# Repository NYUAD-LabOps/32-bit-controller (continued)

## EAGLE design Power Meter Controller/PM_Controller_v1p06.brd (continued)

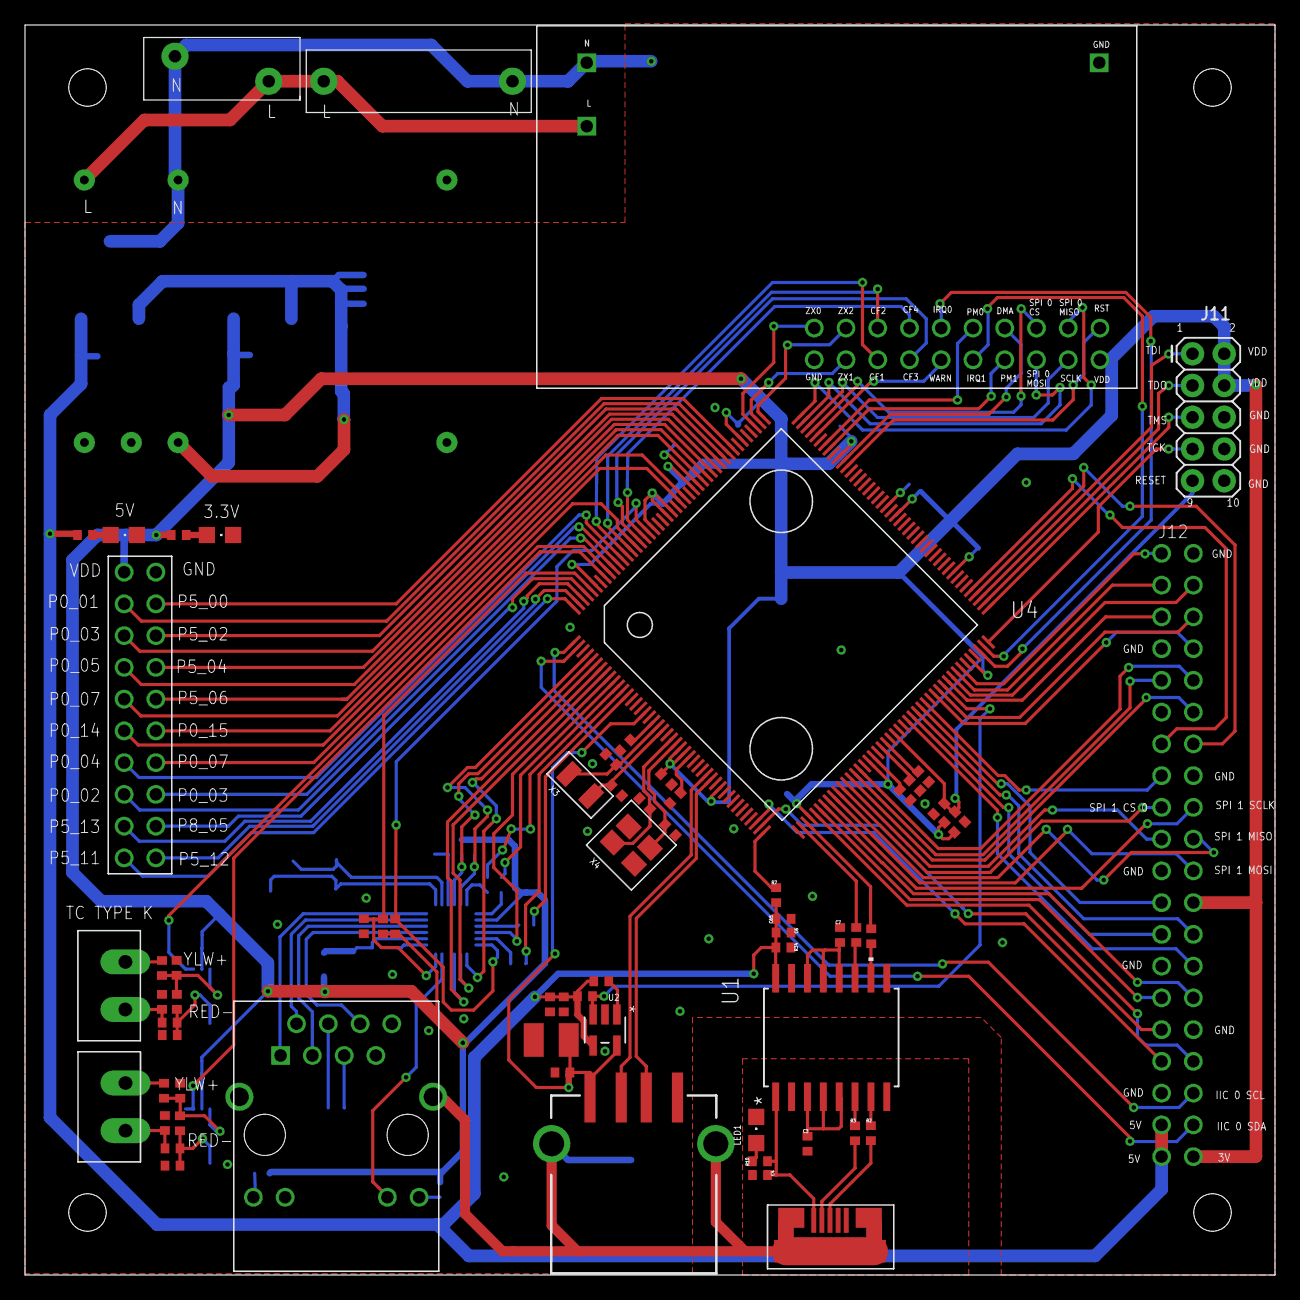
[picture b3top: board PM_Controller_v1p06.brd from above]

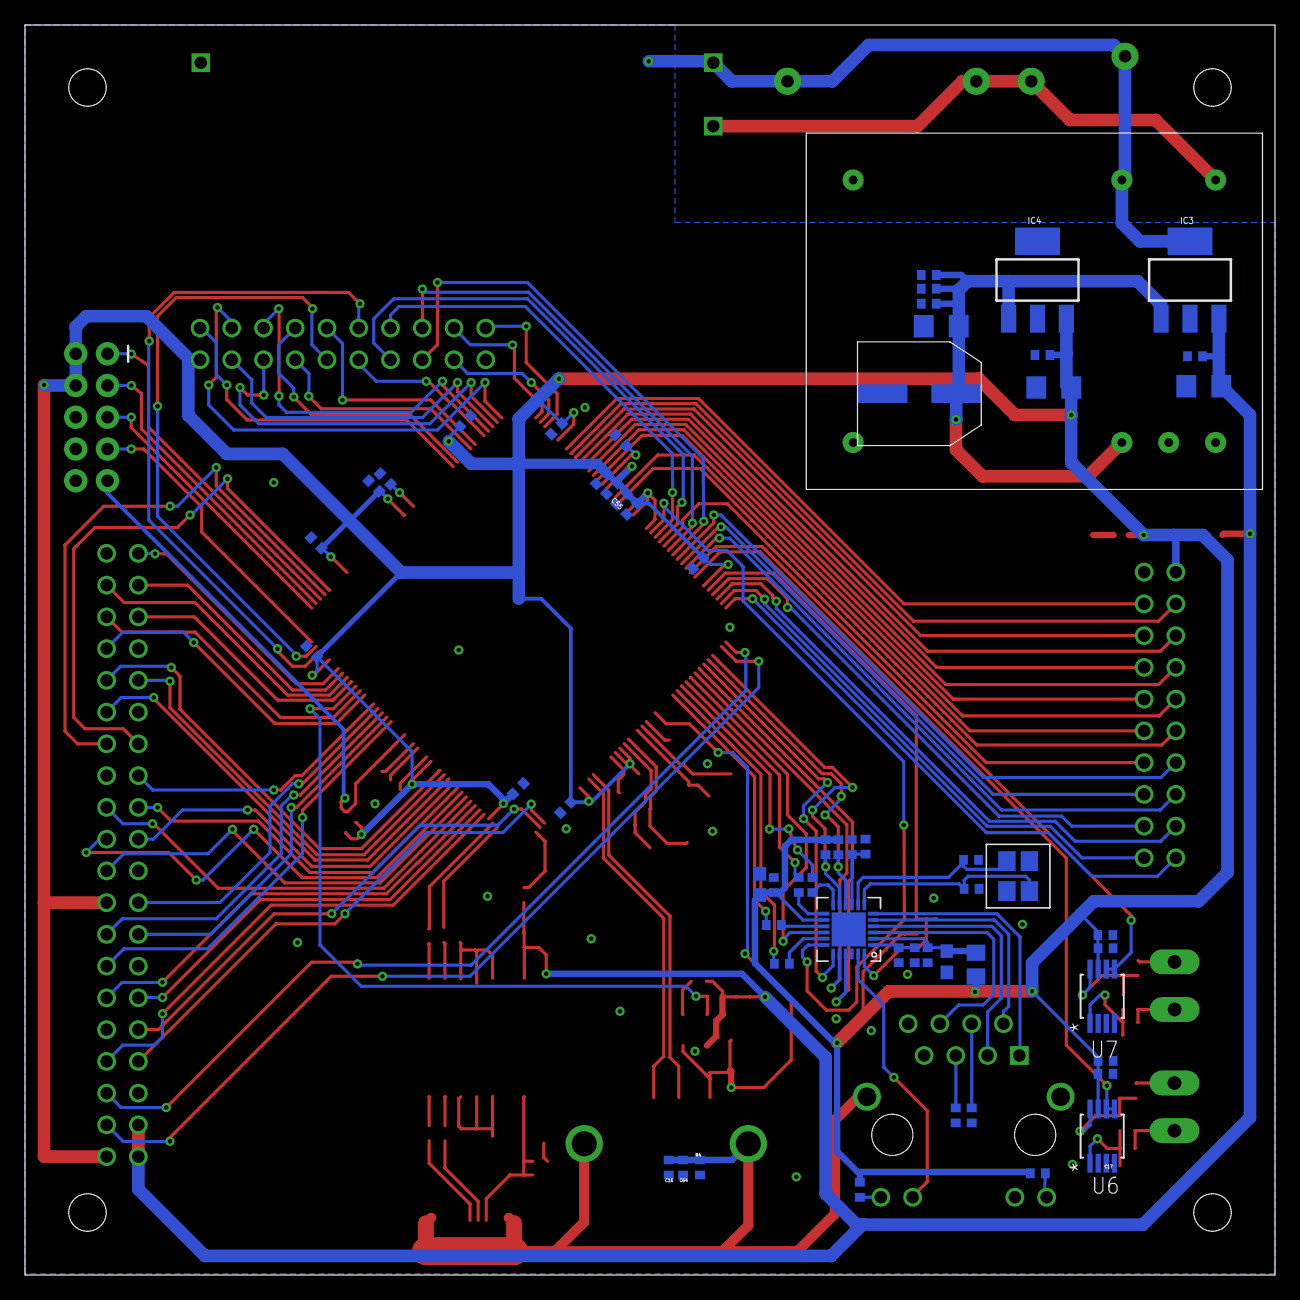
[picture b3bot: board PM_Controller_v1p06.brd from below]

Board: 2 copper layers, 100.0 x 100.0 mm, 125 parts (58 on the bottom side), 147 nets.

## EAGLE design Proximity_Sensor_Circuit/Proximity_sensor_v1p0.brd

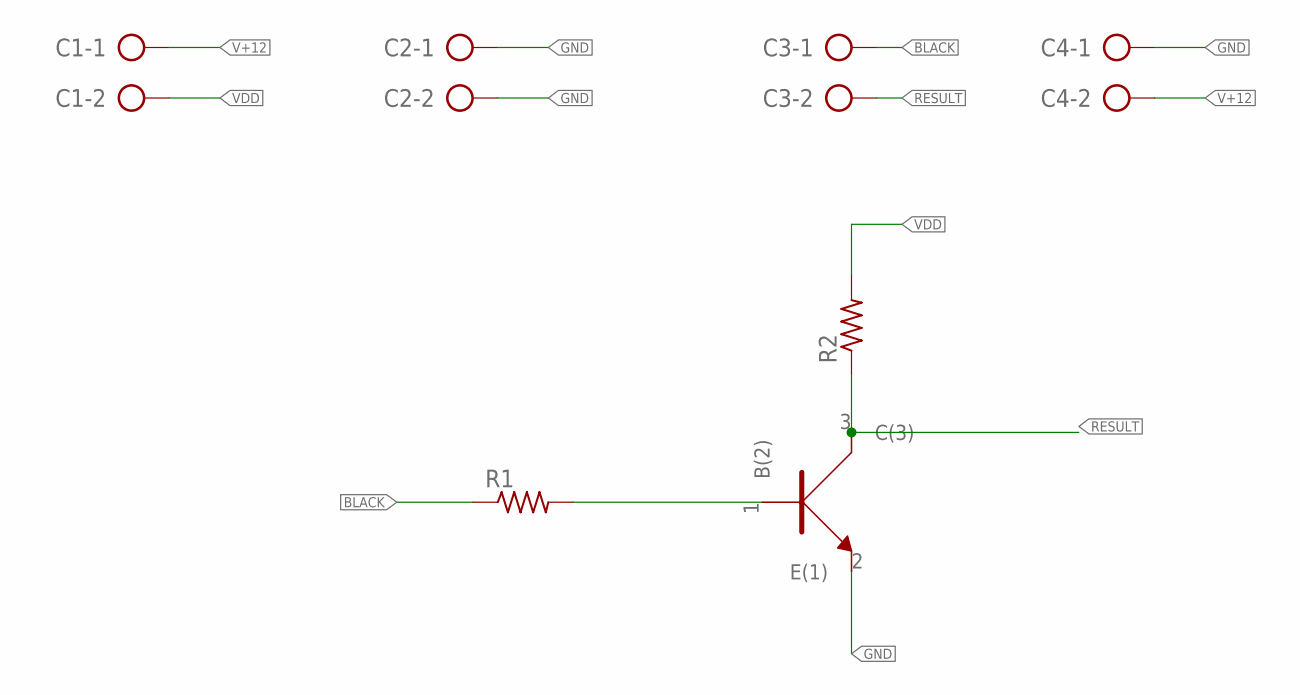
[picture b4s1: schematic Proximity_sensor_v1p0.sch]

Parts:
C1, C2, C3, C4: AK300/2
R1, R2: R_0805; 0805
U1: BC846BW; SOT323

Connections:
BLACK: C3.1, R1.1
GND: C2.1, C2.2, C4.1, U1.2 (E(1))
unnamed: R1.2, U1.1 (B(2))
RESULT: C3.2, R2.1, U1.3 (C(3))
V+12: C1.1, C4.2
VDD: C1.2, R2.2

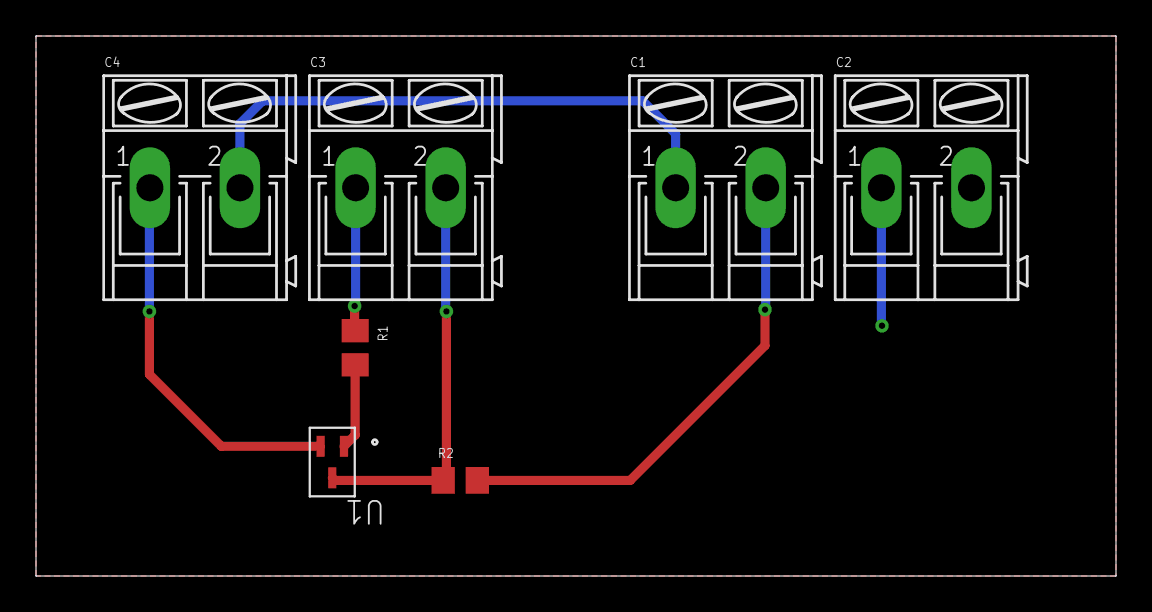
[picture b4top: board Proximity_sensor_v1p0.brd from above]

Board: 2 copper layers, 60.0 x 30.0 mm, 7 parts (0 on the bottom side), 6 nets.

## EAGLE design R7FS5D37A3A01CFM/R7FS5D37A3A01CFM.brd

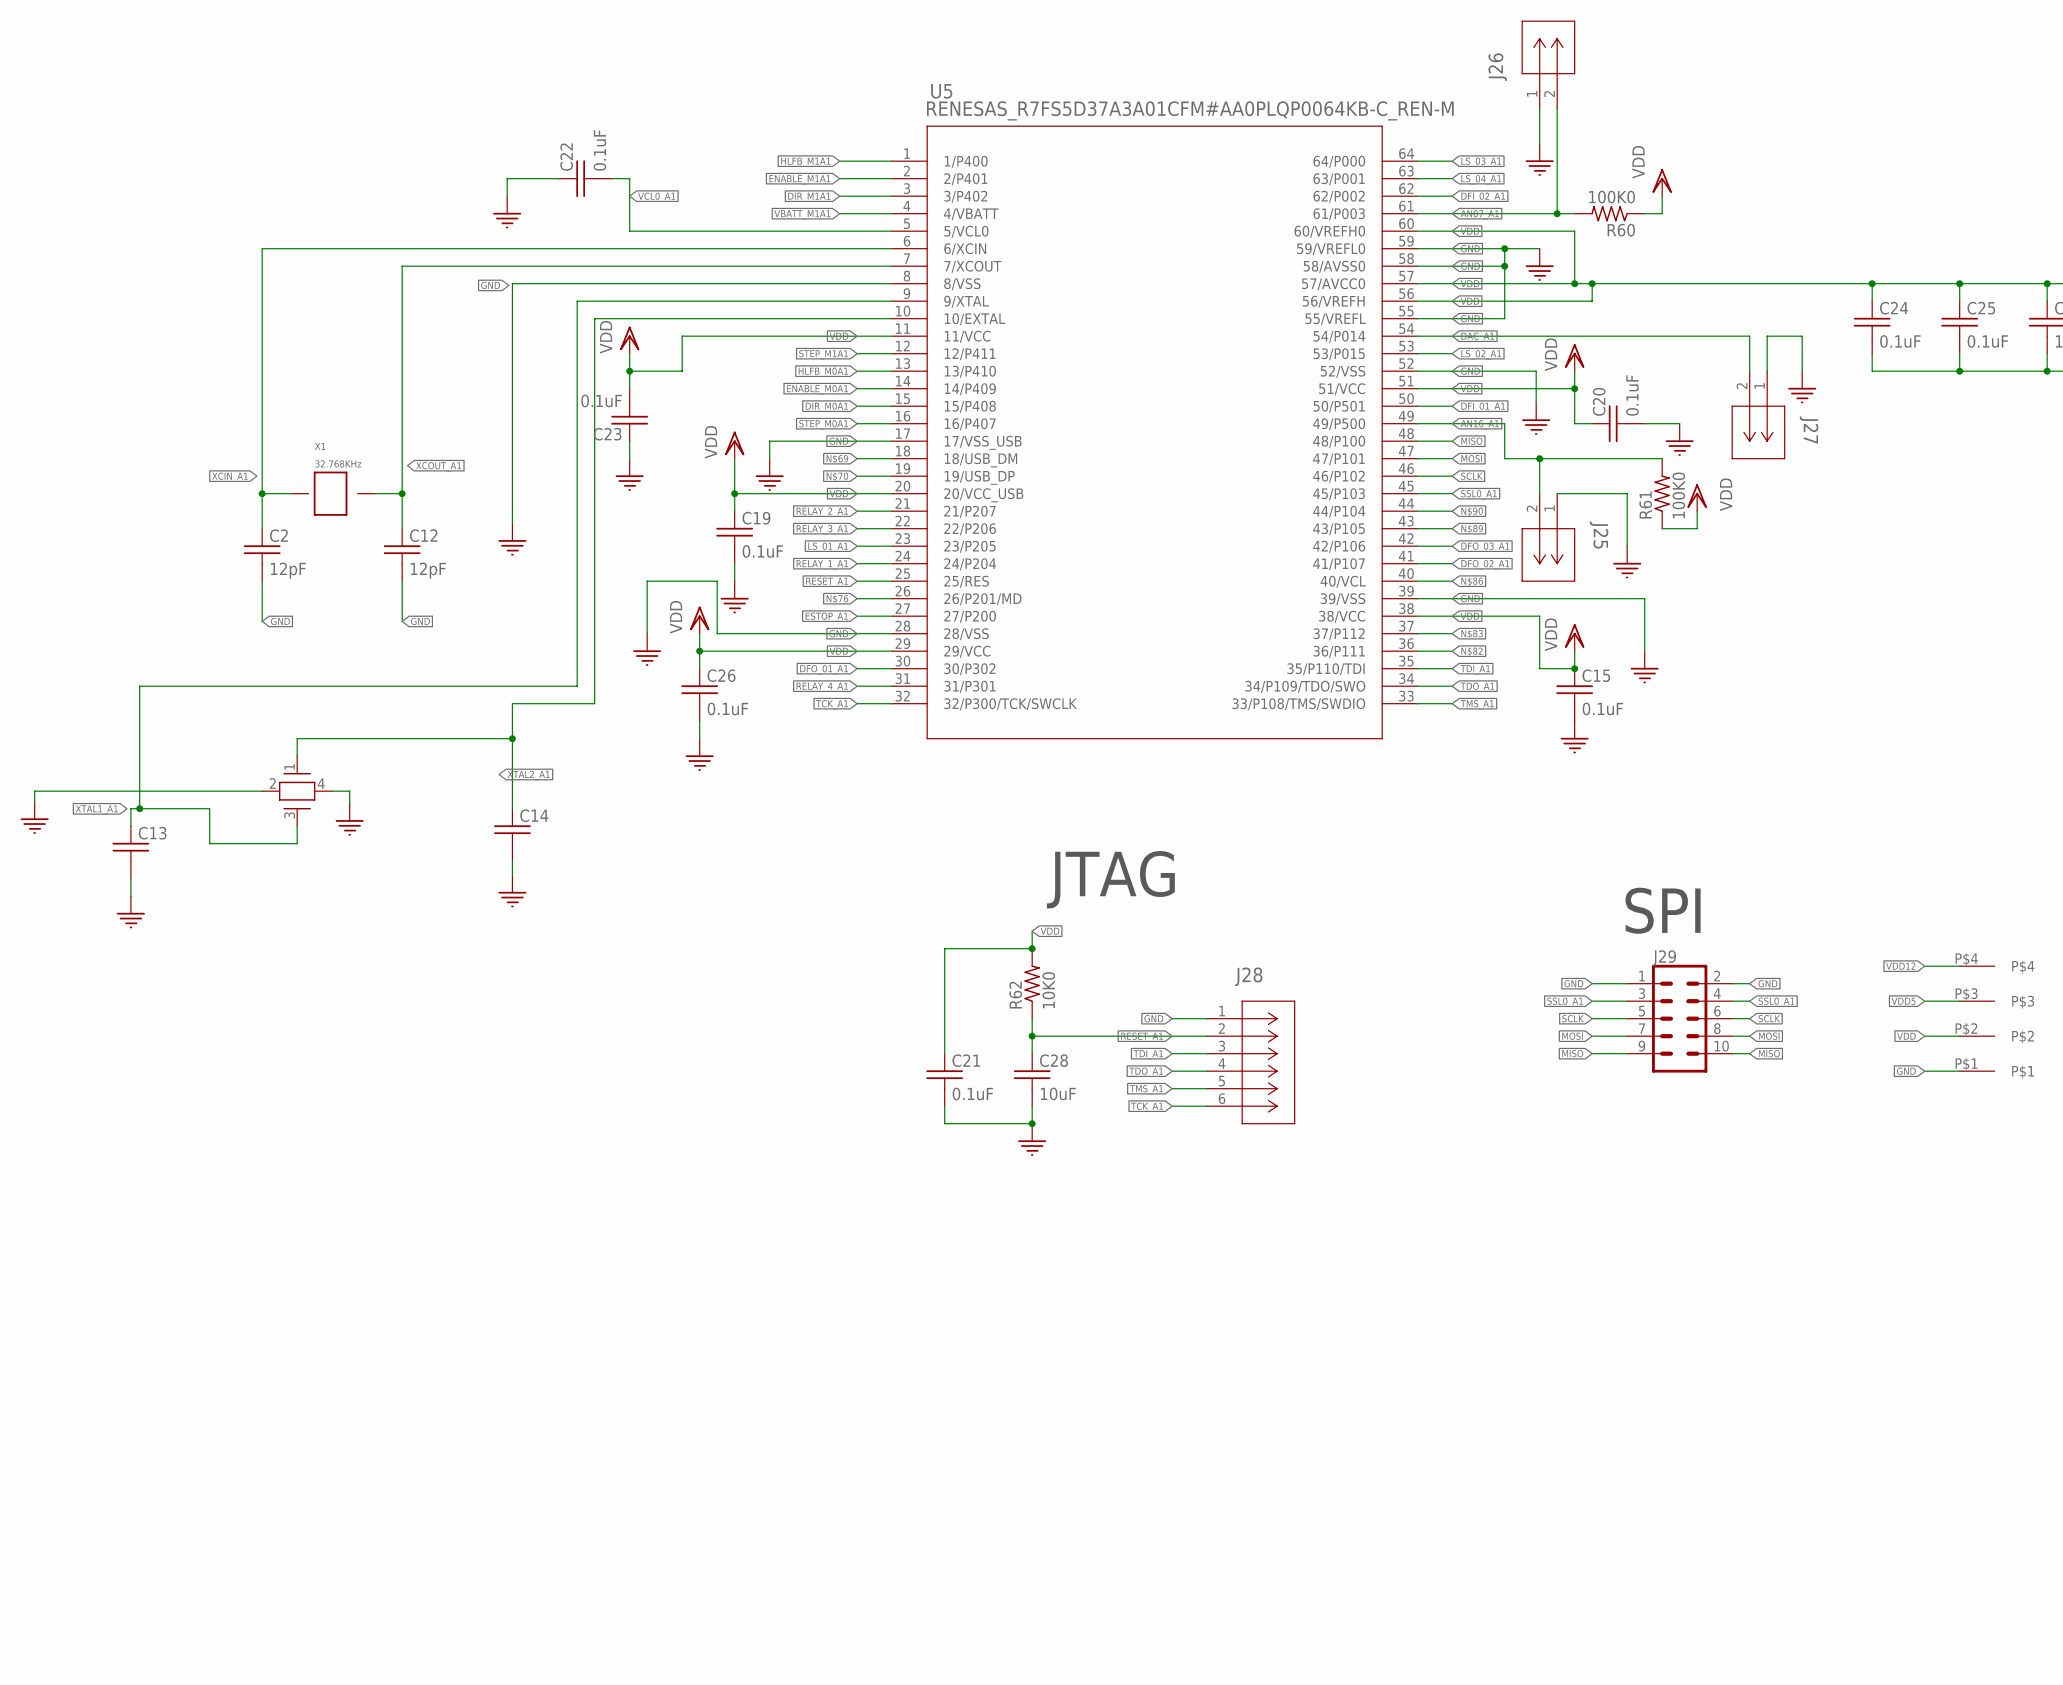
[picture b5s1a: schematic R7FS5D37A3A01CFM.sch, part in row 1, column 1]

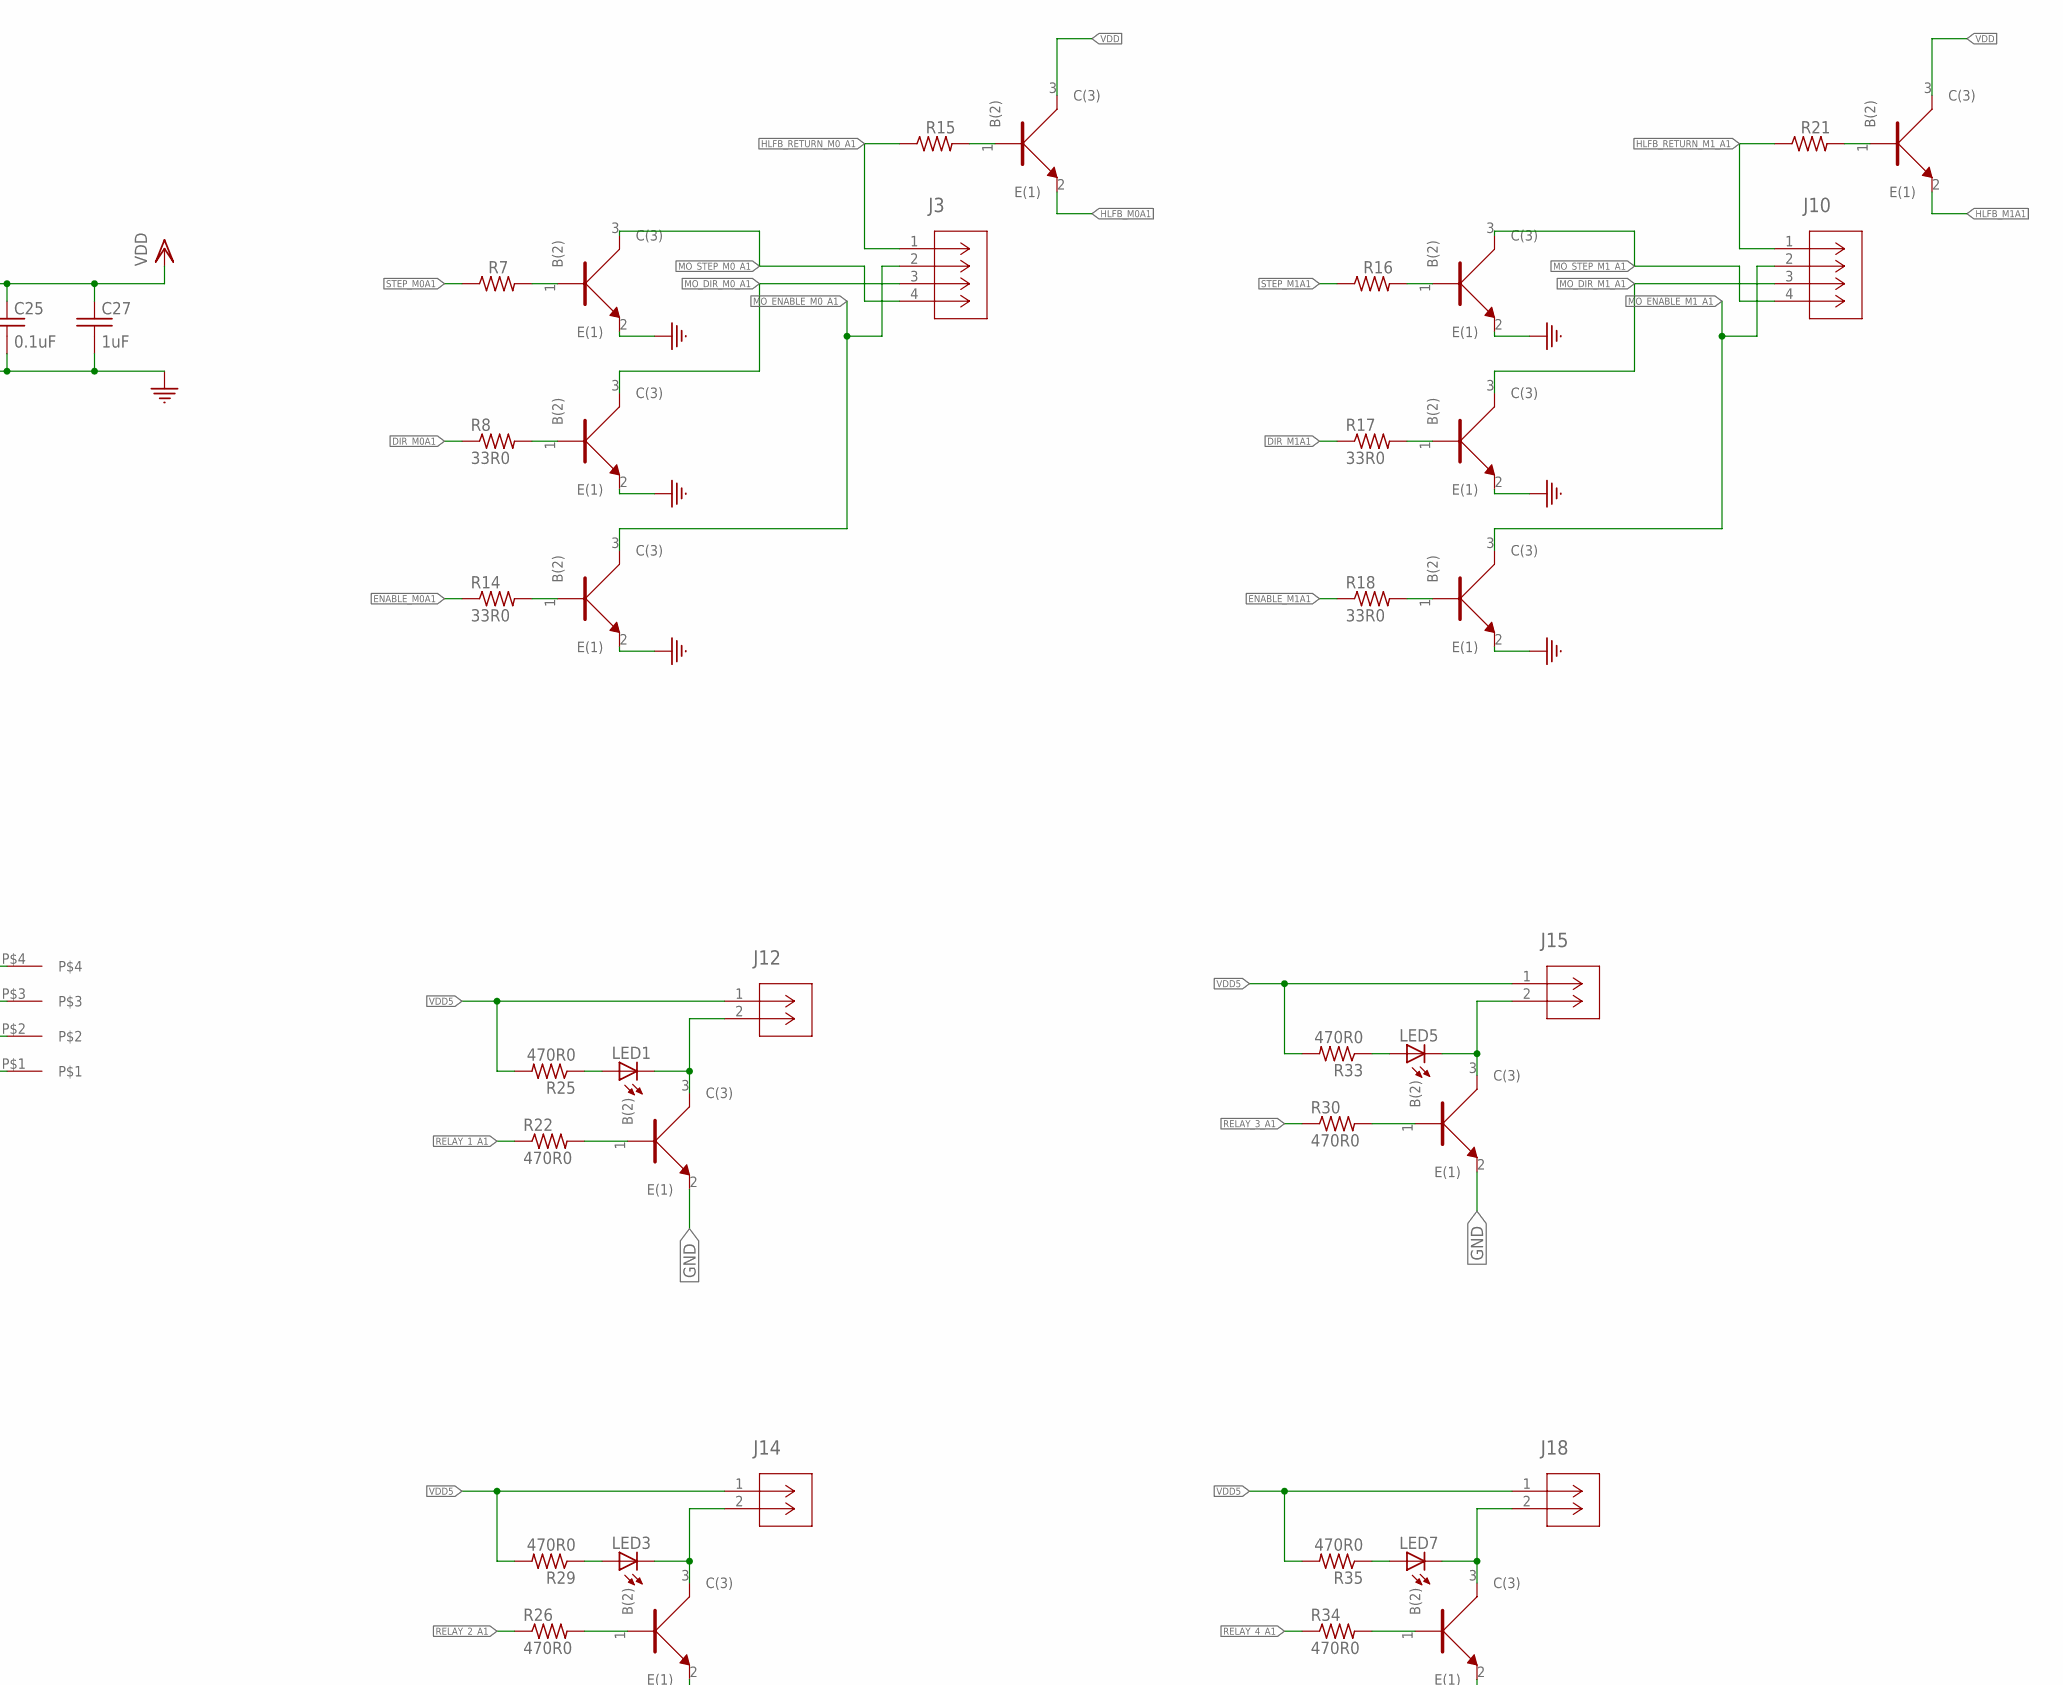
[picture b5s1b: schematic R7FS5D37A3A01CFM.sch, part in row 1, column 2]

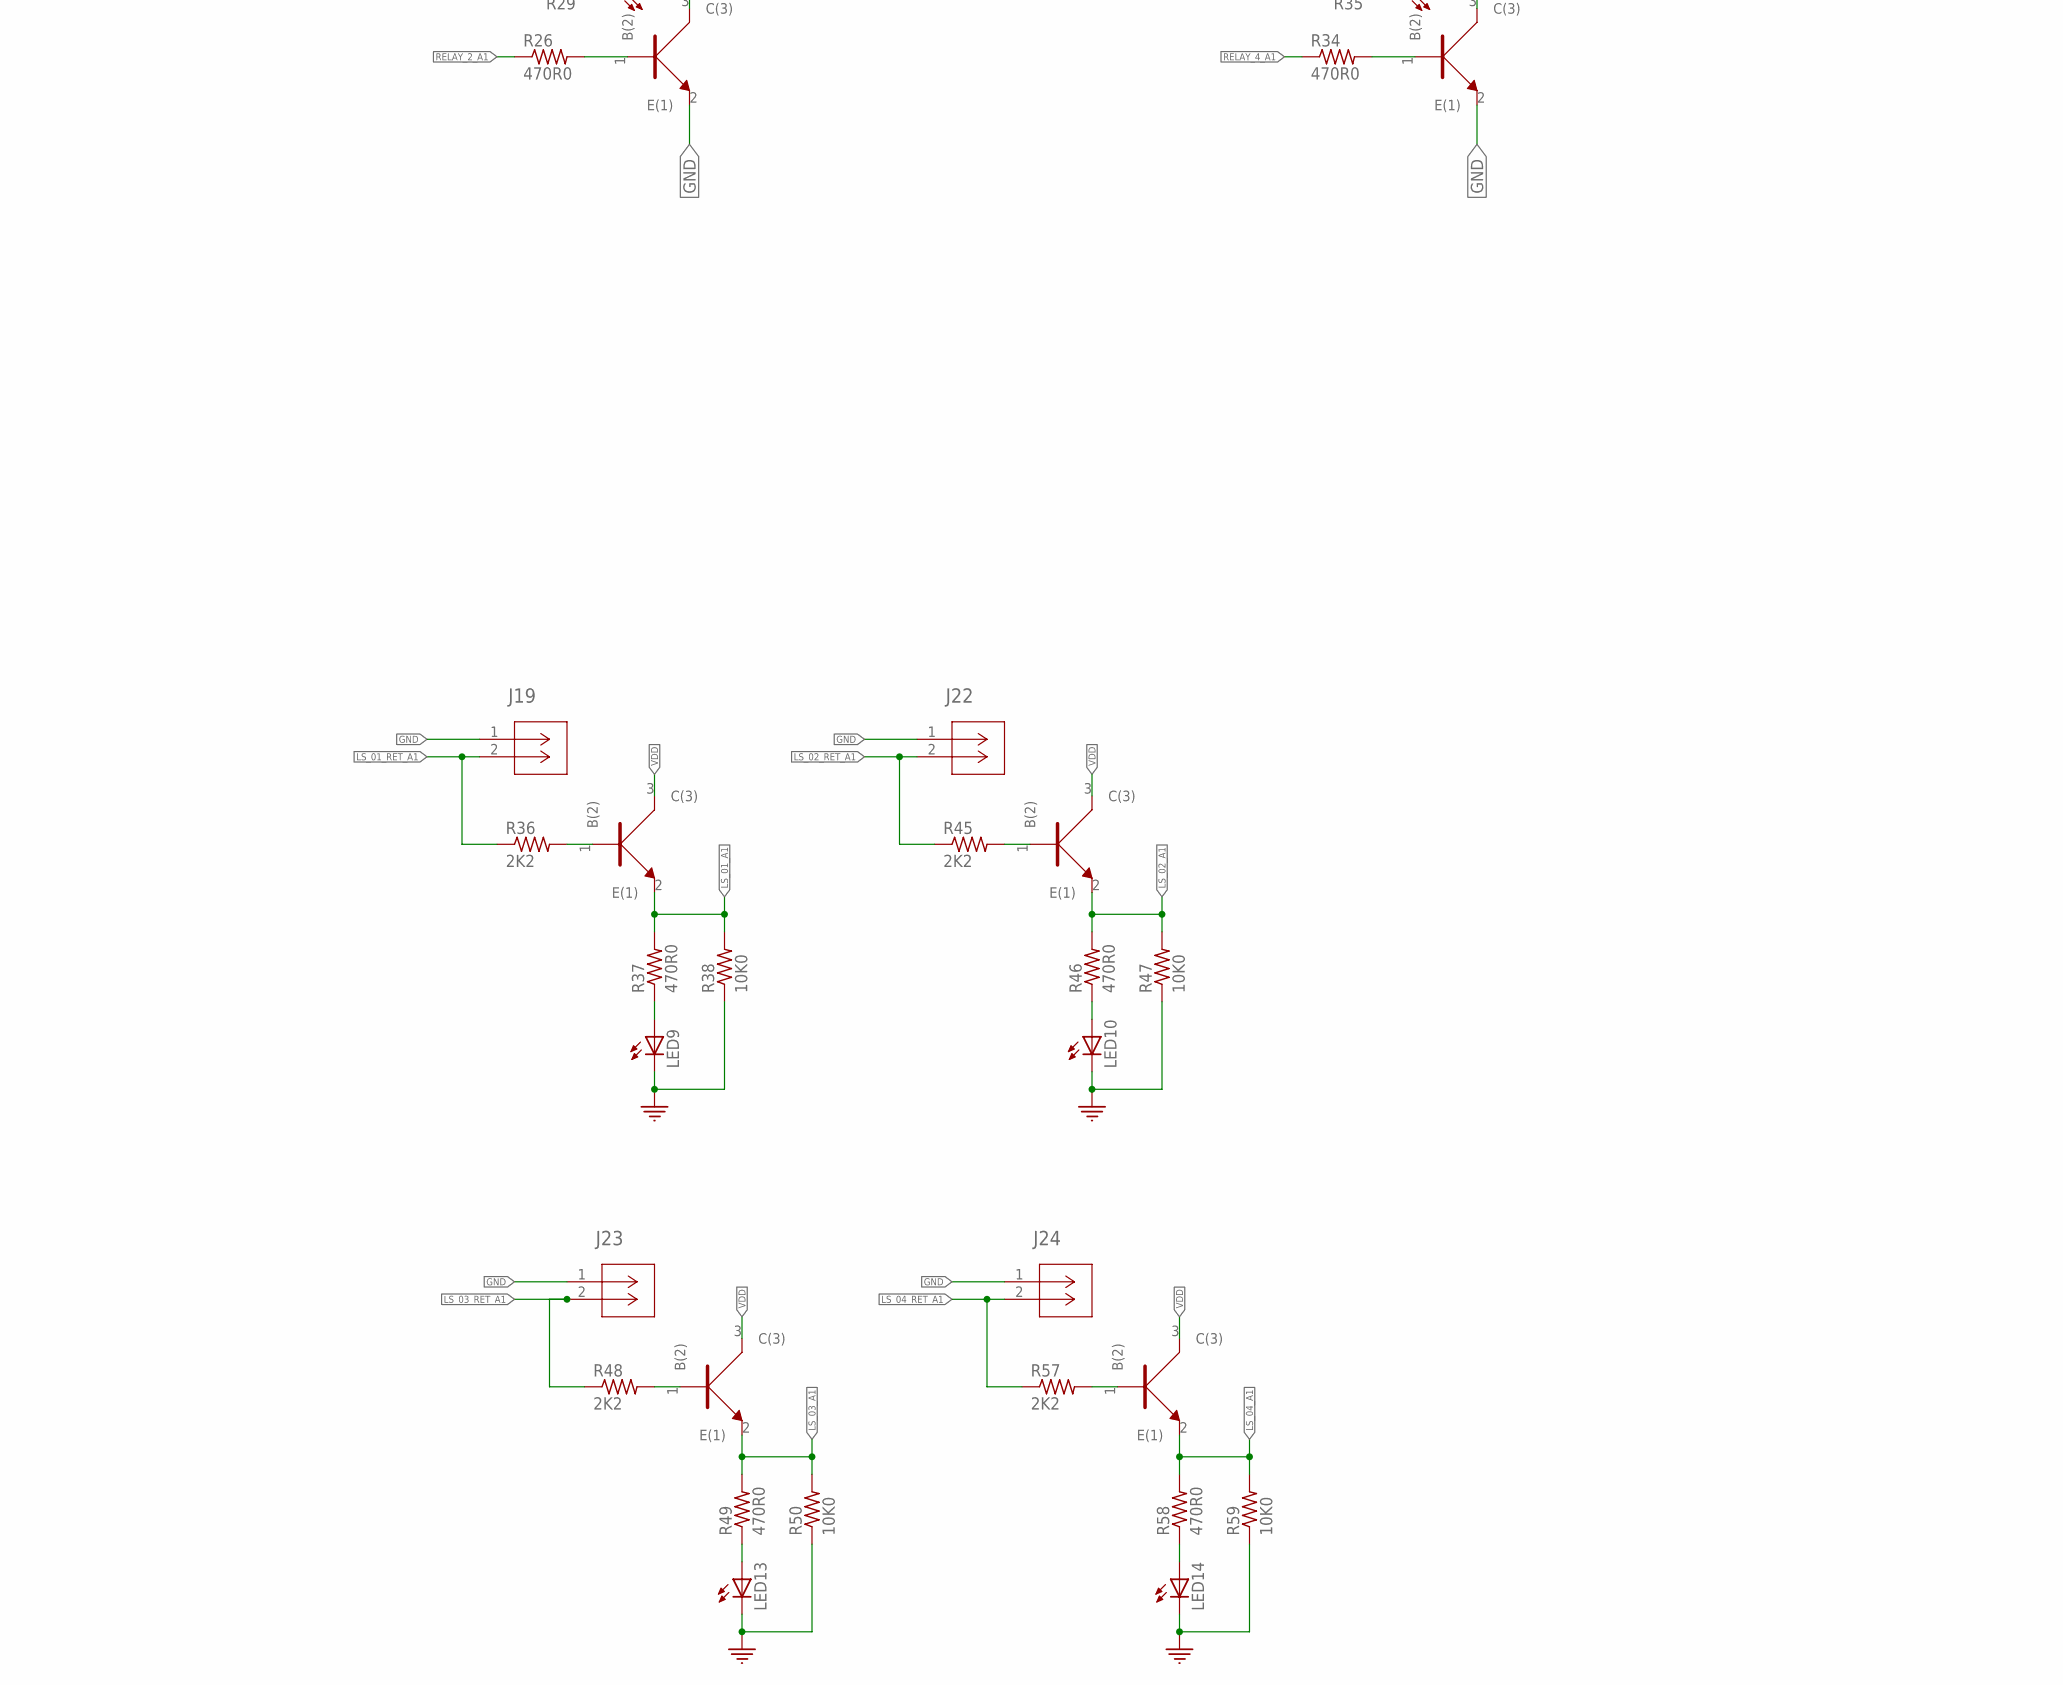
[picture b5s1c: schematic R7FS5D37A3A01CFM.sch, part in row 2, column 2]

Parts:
C2, C12: 12pF; 0402
C13, C14: 10pF; 0402
C15, C19, C20, C21, C22, C23, C24, C25, C26: 0.1uF; 0402
C27: 1uF; 0402
C28: 10uF; 0402
J1: 4-pos; 1X4_3.81MM_PITCH
J3, J10: CONN_530470410_PICOBLADE_X_4; CON_530470410_MOL
J12, J14, J15, J18, J19, J22, J23, J24, J25, J26, J27: CONN_530470210_PICOBLADE_X_2; CON_530470210_MOL
J28: CONN_530470610_PICOBLADE_X_6; CON_530470610_MOL
J29: CONN_05X2PTH; 2X5
LED1, LED3, LED5, LED7, LED9, LED10, LED13, LED14: Green; 0805
R7, R8, R14, R15, R16, R17, R18, R21: 33R0; 0402
R22, R25, R26, R29, R30, R33, R34, R35, R37, R46, R49, R58: 470R0; 0402
R36, R45, R48, R57: 2K2; 0402
R38, R47, R50, R59, R62: 10K0; 0402
R60, R61: 100K0; 0402
U5: RENESAS_R7FS5D37A3A01CFM#AA0PLQP0064KB-C_REN-M; PLQP0064KB-C_REN-M
U6, U7, U8, U13, U14, U15, U16, U18, U20, U22, U24, U26, U27, U30, U31, U34: NPN; SOT323
X1: 32.768KHz; SMD_X_2_PADS
Y2: XTAL_12MHZ_ABM8G-12.000MHZ-B4Y-T; CRYSTAL_ABM8G_ABR

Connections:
AN07_A1: J26.2, R60.P$2 (2), U5.61 (61/P003)
AN16_A1: J25.2, R61.P$2 (2), U5.49 (49/P500)
DAC_A1: J27.2, U5.54 (54/P014)
DFI_01_A1: U5.50 (50/P501)
DFI_02_A1: U5.62 (62/P002)
DFO_01_A1: U5.30 (30/P302)
DFO_02_A1: U5.41 (41/P107)
DFO_03_A1: U5.42 (42/P106)
DIR_M0A1: R8.P$1 (1), U5.15 (15/P408)
DIR_M1A1: R17.P$1 (1), U5.3 (3/P402)
ENABLE_M0A1: R14.P$1 (1), U5.14 (14/P409)
ENABLE_M1A1: R18.P$1 (1), U5.2 (2/P401)
ESTOP_A1: U5.27 (27/P200)
GND: C2.P$2 (2), C12.P$2 (2), C13.P$2 (2), C14.P$2 (2), C15.P$2 (2), C19.P$2 (2), C20.P$2 (2), C21.P$2 (2), C22.P$1 (1), C23.P$1 (1), C24.P$2 (2), C25.P$2 (2), C26.P$2 (2), C27.P$2 (2), C28.P$2 (2), J1.P$1, J19.1, J22.1, J23.1, J24.1, J25.1, J26.1, J27.1, J28.1, J29.1, J29.2, LED9.2 (C), LED10.2 (C), LED13.2 (C), LED14.2 (C), R38.P$1 (1), R47.P$1 (1), R50.P$1 (1), R59.P$1 (1), U5.8 (8/VSS), U5.17 (17/VSS_USB), U5.28 (28/VSS), U5.39 (39/VSS), U5.52 (52/VSS), U5.55 (55/VREFL), U5.58 (58/AVSS0), U5.59 (59/VREFL0), U6.2 (E(1)), U7.2 (E(1)), U8.2 (E(1)), U14.2 (E(1)), U15.2 (E(1)), U16.2 (E(1)), U20.2 (E(1)), U22.2 (E(1)), U24.2 (E(1)), U26.2 (E(1)), Y2.2, Y2.4
HLFB_M0A1: U5.13 (13/P410), U13.2 (E(1))
HLFB_M1A1: U5.1 (1/P400), U18.2 (E(1))
HLFB_RETURN_M0_A1: J3.1, R15.P$1 (1)
HLFB_RETURN_M1_A1: J10.1, R21.P$1 (1)
LS_01_A1: R37.P$2 (2), R38.P$2 (2), U5.23 (23/P205), U27.2 (E(1))
LS_01_RET_A1: J19.2, R36.P$1 (1)
LS_02_A1: R46.P$2 (2), R47.P$2 (2), U5.53 (53/P015), U30.2 (E(1))
LS_02_RET_A1: J22.2, R45.P$1 (1)
LS_03_A1: R49.P$2 (2), R50.P$2 (2), U5.64 (64/P000), U31.2 (E(1))
LS_03_RET_A1: J23.2, R48.P$1 (1)
LS_04_A1: R58.P$2 (2), R59.P$2 (2), U5.63 (63/P001), U34.2 (E(1))
LS_04_RET_A1: J24.2, R57.P$1 (1)
MISO: J29.9, J29.10, U5.48 (48/P100)
MOSI: J29.7, J29.8, U5.47 (47/P101)
MO_DIR_M0_A1: J3.3, U7.3 (C(3))
MO_DIR_M1_A1: J10.3, U15.3 (C(3))
MO_ENABLE_M0_A1: J3.2, U8.3 (C(3))
MO_ENABLE_M1_A1: J10.2, U16.3 (C(3))
MO_STEP_M0_A1: J3.4, U6.3 (C(3))
MO_STEP_M1_A1: J10.4, U14.3 (C(3))
unnamed: R8.P$2 (2), U7.1 (B(2))
unnamed: R14.P$2 (2), U8.1 (B(2))
unnamed: R7.P$2 (2), U6.1 (B(2))
unnamed: R15.P$2 (2), U13.1 (B(2))
unnamed: R17.P$2 (2), U15.1 (B(2))
unnamed: R18.P$2 (2), U16.1 (B(2))
unnamed: R16.P$2 (2), U14.1 (B(2))
unnamed: R21.P$2 (2), U18.1 (B(2))
unnamed: R22.P$2 (2), U20.1 (B(2))
unnamed: J12.2, LED1.2 (C), U20.3 (C(3))
unnamed: LED1.1 (A), R25.P$1 (1)
unnamed: R26.P$2 (2), U22.1 (B(2))
unnamed: J14.2, LED3.2 (C), U22.3 (C(3))
unnamed: LED3.1 (A), R29.P$1 (1)
unnamed: R30.P$2 (2), U24.1 (B(2))
unnamed: J15.2, LED5.2 (C), U24.3 (C(3))
unnamed: LED5.1 (A), R33.P$1 (1)
unnamed: R34.P$2 (2), U26.1 (B(2))
unnamed: J18.2, LED7.2 (C), U26.3 (C(3))
unnamed: LED7.1 (A), R35.P$1 (1)
unnamed: R36.P$2 (2), U27.1 (B(2))
unnamed: LED9.1 (A), R37.P$1 (1)
unnamed: R45.P$2 (2), U30.1 (B(2))
unnamed: LED10.1 (A), R46.P$1 (1)
unnamed: R48.P$2 (2), U31.1 (B(2))
unnamed: LED13.1 (A), R49.P$1 (1)
unnamed: R57.P$2 (2), U34.1 (B(2))
unnamed: LED14.1 (A), R58.P$1 (1)
RELAY_1_A1: R22.P$1 (1), U5.24 (24/P204)
RELAY_2_A1: R26.P$1 (1), U5.21 (21/P207)
RELAY_3_A1: R30.P$1 (1), U5.22 (22/P206)
RELAY_4_A1: R34.P$1 (1), U5.31 (31/P301)
RESET_A1: C28.P$1 (1), J28.2, R62.P$1 (1), U5.25 (25/RES)
SCLK: J29.5, J29.6, U5.46 (46/P102)
SSL0_A1: J29.3, J29.4, U5.45 (45/P103)
STEP_M0A1: R7.P$1 (1), U5.16 (16/P407)
STEP_M1A1: R16.P$1 (1), U5.12 (12/P411)
TCK_A1: J28.6, U5.32 (32/P300/TCK/SWCLK)
TDI_A1: J28.3, U5.35 (35/P110/TDI)
TDO_A1: J28.4, U5.34 (34/P109/TDO/SWO)
TMS_A1: J28.5, U5.33 (33/P108/TMS/SWDIO)
VBATT_M1A1: U5.4 (4/VBATT)
VCL0_A1: C22.P$2 (2), U5.5 (5/VCL0)
VDD: C15.P$1 (1), C19.P$1 (1), C20.P$1 (1), C21.P$1 (1), C23.P$2 (2), C24.P$1 (1), C25.P$1 (1), C26.P$1 (1), C27.P$1 (1), J1.P$2, R60.P$1 (1), R61.P$1 (1), R62.P$2 (2), U5.11 (11/VCC), U5.20 (20/VCC_USB), U5.29 (29/VCC), U5.38 (38/VCC), U5.51 (51/VCC), U5.56 (56/VREFH), U5.57 (57/AVCC0), U5.60 (60/VREFH0), U13.3 (C(3)), U18.3 (C(3)), U27.3 (C(3)), U30.3 (C(3)), U31.3 (C(3)), U34.3 (C(3))
VDD5: J1.P$3, J12.1, J14.1, J15.1, J18.1, R25.P$2 (2), R29.P$2 (2), R33.P$2 (2), R35.P$2 (2)
VDD12: J1.P$4
XCIN_A1: C2.P$1 (1), U5.6 (6/XCIN), X1.P$1
XCOUT_A1: C12.P$1 (1), U5.7 (7/XCOUT), X1.P$2
XTAL1_A1: C13.P$1 (1), U5.9 (9/XTAL), Y2.3
XTAL2_A1: C14.P$1 (1), U5.10 (10/EXTAL), Y2.1

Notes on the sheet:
JTAG
SPI

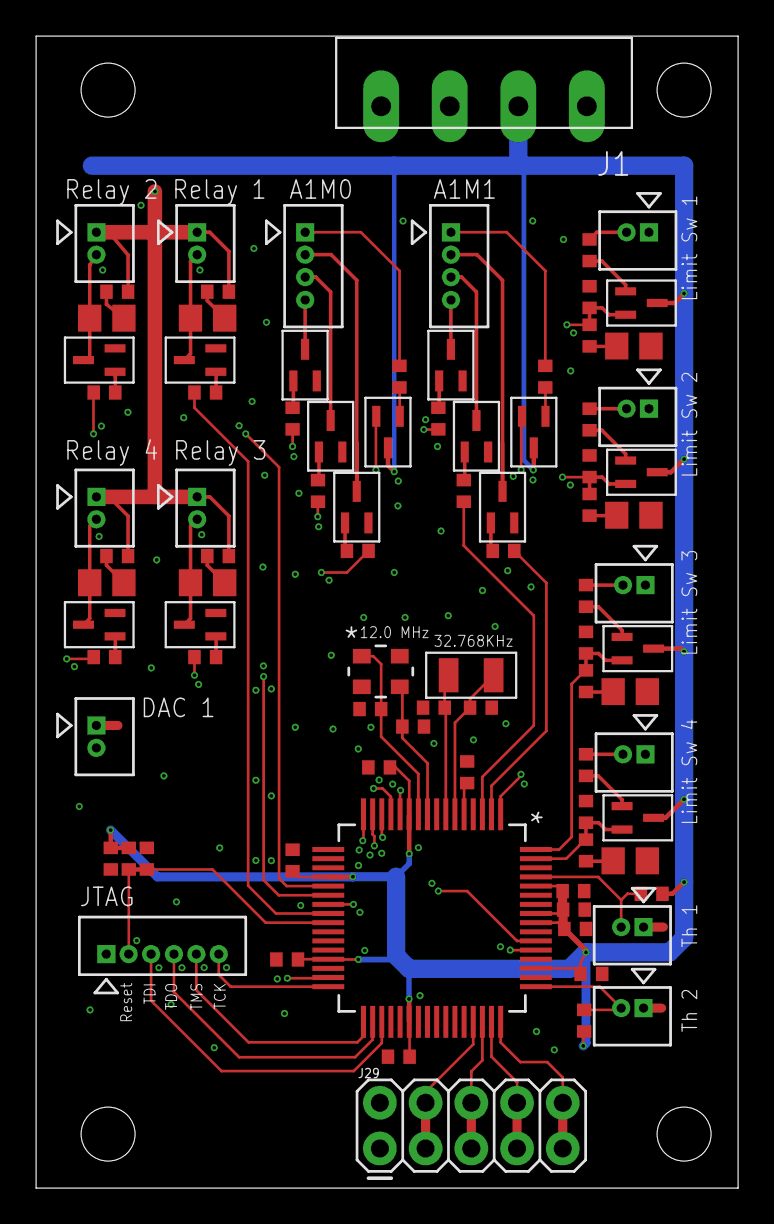
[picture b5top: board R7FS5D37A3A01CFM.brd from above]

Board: 6 copper layers, 39.0 x 64.0 mm, 89 parts (0 on the bottom side), 76 nets.
